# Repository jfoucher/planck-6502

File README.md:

# Planck computer

# An open hardware, extensible 65c02 based computer

This is a hobby computer based on the 65C02 processor. (I use 6502 and 65C02 interchangeably in this document, but [there are some differences](http://wilsonminesco.com/NMOS-CMOSdif/))

There are already many computers based on the 6502 processor, old ones such as as the Apple 1, Apple II, Commodore 64 and many more; and many more recent ones, from homebrew affairs on prototype board, to complete replicas of old systems.

The one that most closely resembles the Planck is probably the RC6502, itself based on the RC2014 (which uses a Z80 processor) with adaptations to the expansion bus to make it fit the 6502 processor.

Planck is a new variant on this type of expandable machines with a different set of tradeoffs.

### Contraints and requirements

The constraints for it's design were the following:

  - Minimum board size, 2 layers, as that is what is cheapest to have fabricated.
  - Easily extensible with for example:
    - Serial port
    - Parallel port
    - SPI / SPI65B port
    - PS/2 port for keyboard
    - Sound card
    - VGA out
    - SD card
    - LCD screen
  - Target clock speed of 10 to 12 MHz

## Some details

These requirements resulted in a computer based on a [motherboard](/Hardware/mainboard) hosting RAM, ROM and CPU and extension slots for expansion cards to plug into.

The [Planck hardware pages](/Hardware) explains more about the functionality of the motherboard and of each basic extension boards.

Of course, you can [design your own expansion boards](/Hardware/make) to make the computer do whatever **you** decide

### Expansion

Each expansion slot has a signal that should cause it to activate (<span style="text-decoration:overline">SEL1</span> to <span style="text-decoration:overline">SEL5</span> as detailed in the expansion bus description). The signals are generated by a programable logic chip on the motherboard (ATF22V10 or equivalent) according to the address that the processor is currently trying to access.

The main computer clock is generated on the motherboard by an oscillator. The clock signal goes through a binary counter, which makes it possible to slow down the clock when accessing slow devices.

The expansion slots are common 2x25 "Dupont" sockets on 2.54mm (100mil) centers and are very easy to obtain.

#### Expansion bus pinout

Most pins correspond to the pins of the same name on the CPU.

Below are the pins that are specific to the expansion bus:

| Pin number | Pin name | Description |
|-----   |-----|--------|
| 1 | A0 | Processor address bus pin 0 |
| 2 | D0 | Processor data bus pin 0 |
| 3 | A1 | Processor address bus pin 1 |
| 4 | D1 | Processor data bus pin 1 |
| 5 | A2 | Processor address bus pin 2 |
| 6 | D2 | Processor data bus pin 2 |
| 7 | A3 | Processor address bus pin 3 |
| 8 | D3 | Processor data bus pin 3 |
| 9 | A4 | Processor address bus pin 4 |
| 10 | D4 | Processor data bus pin 4 |
| 11 | A5 | Processor address bus pin 5 |
| 12 | D5 | Processor data bus pin 5 |
| 13 | A6 | Processor address bus pin 6 |
| 14 | D6 | Processor data bus pin 6 |
| 15 | A7 | Processor address bus pin 7 |
| 16 | D7 | Processor data bus pin 7 |
| 17 | A8 | Processor address bus pin 8 |
| 18 | EX0 | Extra pin for future use or for communication between expansion cards |
| 19 | A9 | Processor address bus pin 9 |
| 20 | EX1 | Extra pin for future use or for communication between expansion cards |
| 21 | A10 | Processor address bus pin 10 |
| 22 | <span style="text-decoration:overline">SLOW</span> | Used by slow peripherals to request a slower clock speed, active low. |
| 23 | GND | Ground |
| 24 | +5V | Positive voltage |
| 25 | +5V | Positive voltage |
| 26 | GND | Ground |
| 27 | A11 | Processor address bus pin 11 |
| 28 | <span style="text-decoration:overline">SSEL</span> | An expansion card is selected. Used by the processor card to disable it's built-in ram an ROM, active low |
| 29 | A12 | Processor address bus pin 12 |
| 30 | <span style="text-decoration:overline">INH</span> | When this is active (low), processor card RAM and ROM are disabled |
| 31 | A13 | Processor address bus pin 13 |
| 32 | <span style="text-decoration:overline">SLOT_SEL</span> | Used by the backplane to signal to expansion cards when they should activate, active low |
| 33 | A14 | Processor address bus pin 14 |
| 34 | LED1 | Connected to one of the backplane LEDs |
| 35 | A15 | Processor address bus pin 15 |
| 36 | LED2 | Connected to one of the backplane LEDs |
| 37 | RDY | Processor I/O pin. When low, the processor waits in it's curent state |
| 38 | LED3 | Connected to one of the backplane LEDs |
| 39 | BE | Processor input pin. when low the processor releases the bus |
| 40 | LED4 | Connected to one of the backplane LEDs |
| 41 | CLK | Main computer clock. Can be stretched or not depending on the state of the SLOW signal. |
| 42 | CLK_12M | Stable clock for e.g. VIA timers. **Not connected to slot 0** |
| 43 | R<span style="text-decoration:overline">W</span> | CPU read / write pin |
| 44 | EX4 | Extra signal 4. **Not connected to slot 0** |
| 45 | <span style="text-decoration:overline">IRQ</span> | This goes low when an interrupt request has occured, active low |
| 46 | EX5 | Extra signal 5. **Not connected to slot 0** |
| 47 | SYNC | CPU output. Indicates when the CPU is fetching an opcode |
| 48 | <span style="text-decoration:overline">SLOT_IRQ</span> | Used by expansion cards to signal an interrupt request to the processor board, active low  |
| 49 | <span style="text-decoration:overline">RESET</span> | Reset signal trigered by the button on the backplane, active low |
| 50 | <span style="text-decoration:overline">NMI</span> | non maskable interrupt signal trigered by the button on the backplane, active low |

The Planck 6502 computer is a single board computer that communicates over serial, or can be a standalone computer by adding expansion cards to one of the 6 slots present on the motherboard.

### Input / output
Also present on the motherboard are two buttons and 4 LEDs.

One button triggers a reset of the processor, and the other triggers an non-maskable interrupt (<span style="text-decoration:overline">NMI</span>) which can be thought of as a "soft" reset.

The leds are connected to the expansion bus, and so any board can control them. They can be used as a crude debug tool, to show the status of some processing, to try out a simple blink routine or to signal an error to the user.

### Power delivery

The power to the board is provided by a barrel jack at the bottom left. There is a linear regulator on the board, so the power supply voltage can be anywhere from 7V to 12V, although with the latter a heatsink may be required on the regulator.

A power switch and a power LED are also provided on the backplane.

## Available expansion boards

### I/O board

[The IO board](Hardware/io_board) is based on a WDC65C22 chip and provides a keyboard PS/2 port, a parallel port and a 65SIB port (serial port similar to and compatible with SPI)

### Serial board

[The serial board](Hardware/serial_board) is based on a WDC65C51 chip and provides serial output through a TTL serial to USB adapter. When plugging the USB cable to your PC, it may be best to unplug the power from the backplane and let the computer be powered from your PC through the USB to serial adapter.

### OPL2 board

[A sound card](Hardware/opl2_board) based on the Yamaha OPL2 chip found in the original sound blaster card for example.

### LCD board

[This board](Hardware/lcd_board) allow a 20x04 LCD to be connected to the computer for text output.

<br />This documentation is licensed under a <a rel="license" href="http://creativecommons.org/licenses/by-sa/4.0/">Creative Commons Attribution-ShareAlike 4.0 International License</a>.

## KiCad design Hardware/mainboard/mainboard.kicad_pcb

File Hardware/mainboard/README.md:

## Planck computer

This is a complete computer based on the Planck 6502 backplane.

It provides a 65c02 cPU, 32k of RAM, 32k of ROM and a serial port, as well as 6 expansion slots.

The board exceeds the original size specification of the original project (100 x 150mm instead of 100 x 100mm) but it seems that the cost will be similar (one more expensive board replaces 3 cheaper boards) as well as being more practical for some applications.

This computer can run absolutely stand alone when connected via the serial port. It can also accommodate 2 more expansion cards compared to the original backplane.

Here is a 3D view of the board:

You can [download the schematic](https://planck6502.com/fabrication/mainboard-schematic.pdf) and the [gerber files](https://planck6502.com/fabrication/mainboard-zip.zip)

[Documentation](https://planck6502.com/Hardware/io/)

<br />This documentation is licensed under a <a rel="license" href="http://creativecommons.org/licenses/by-sa/4.0/">Creative Commons Attribution-ShareAlike 4.0 International License</a>.

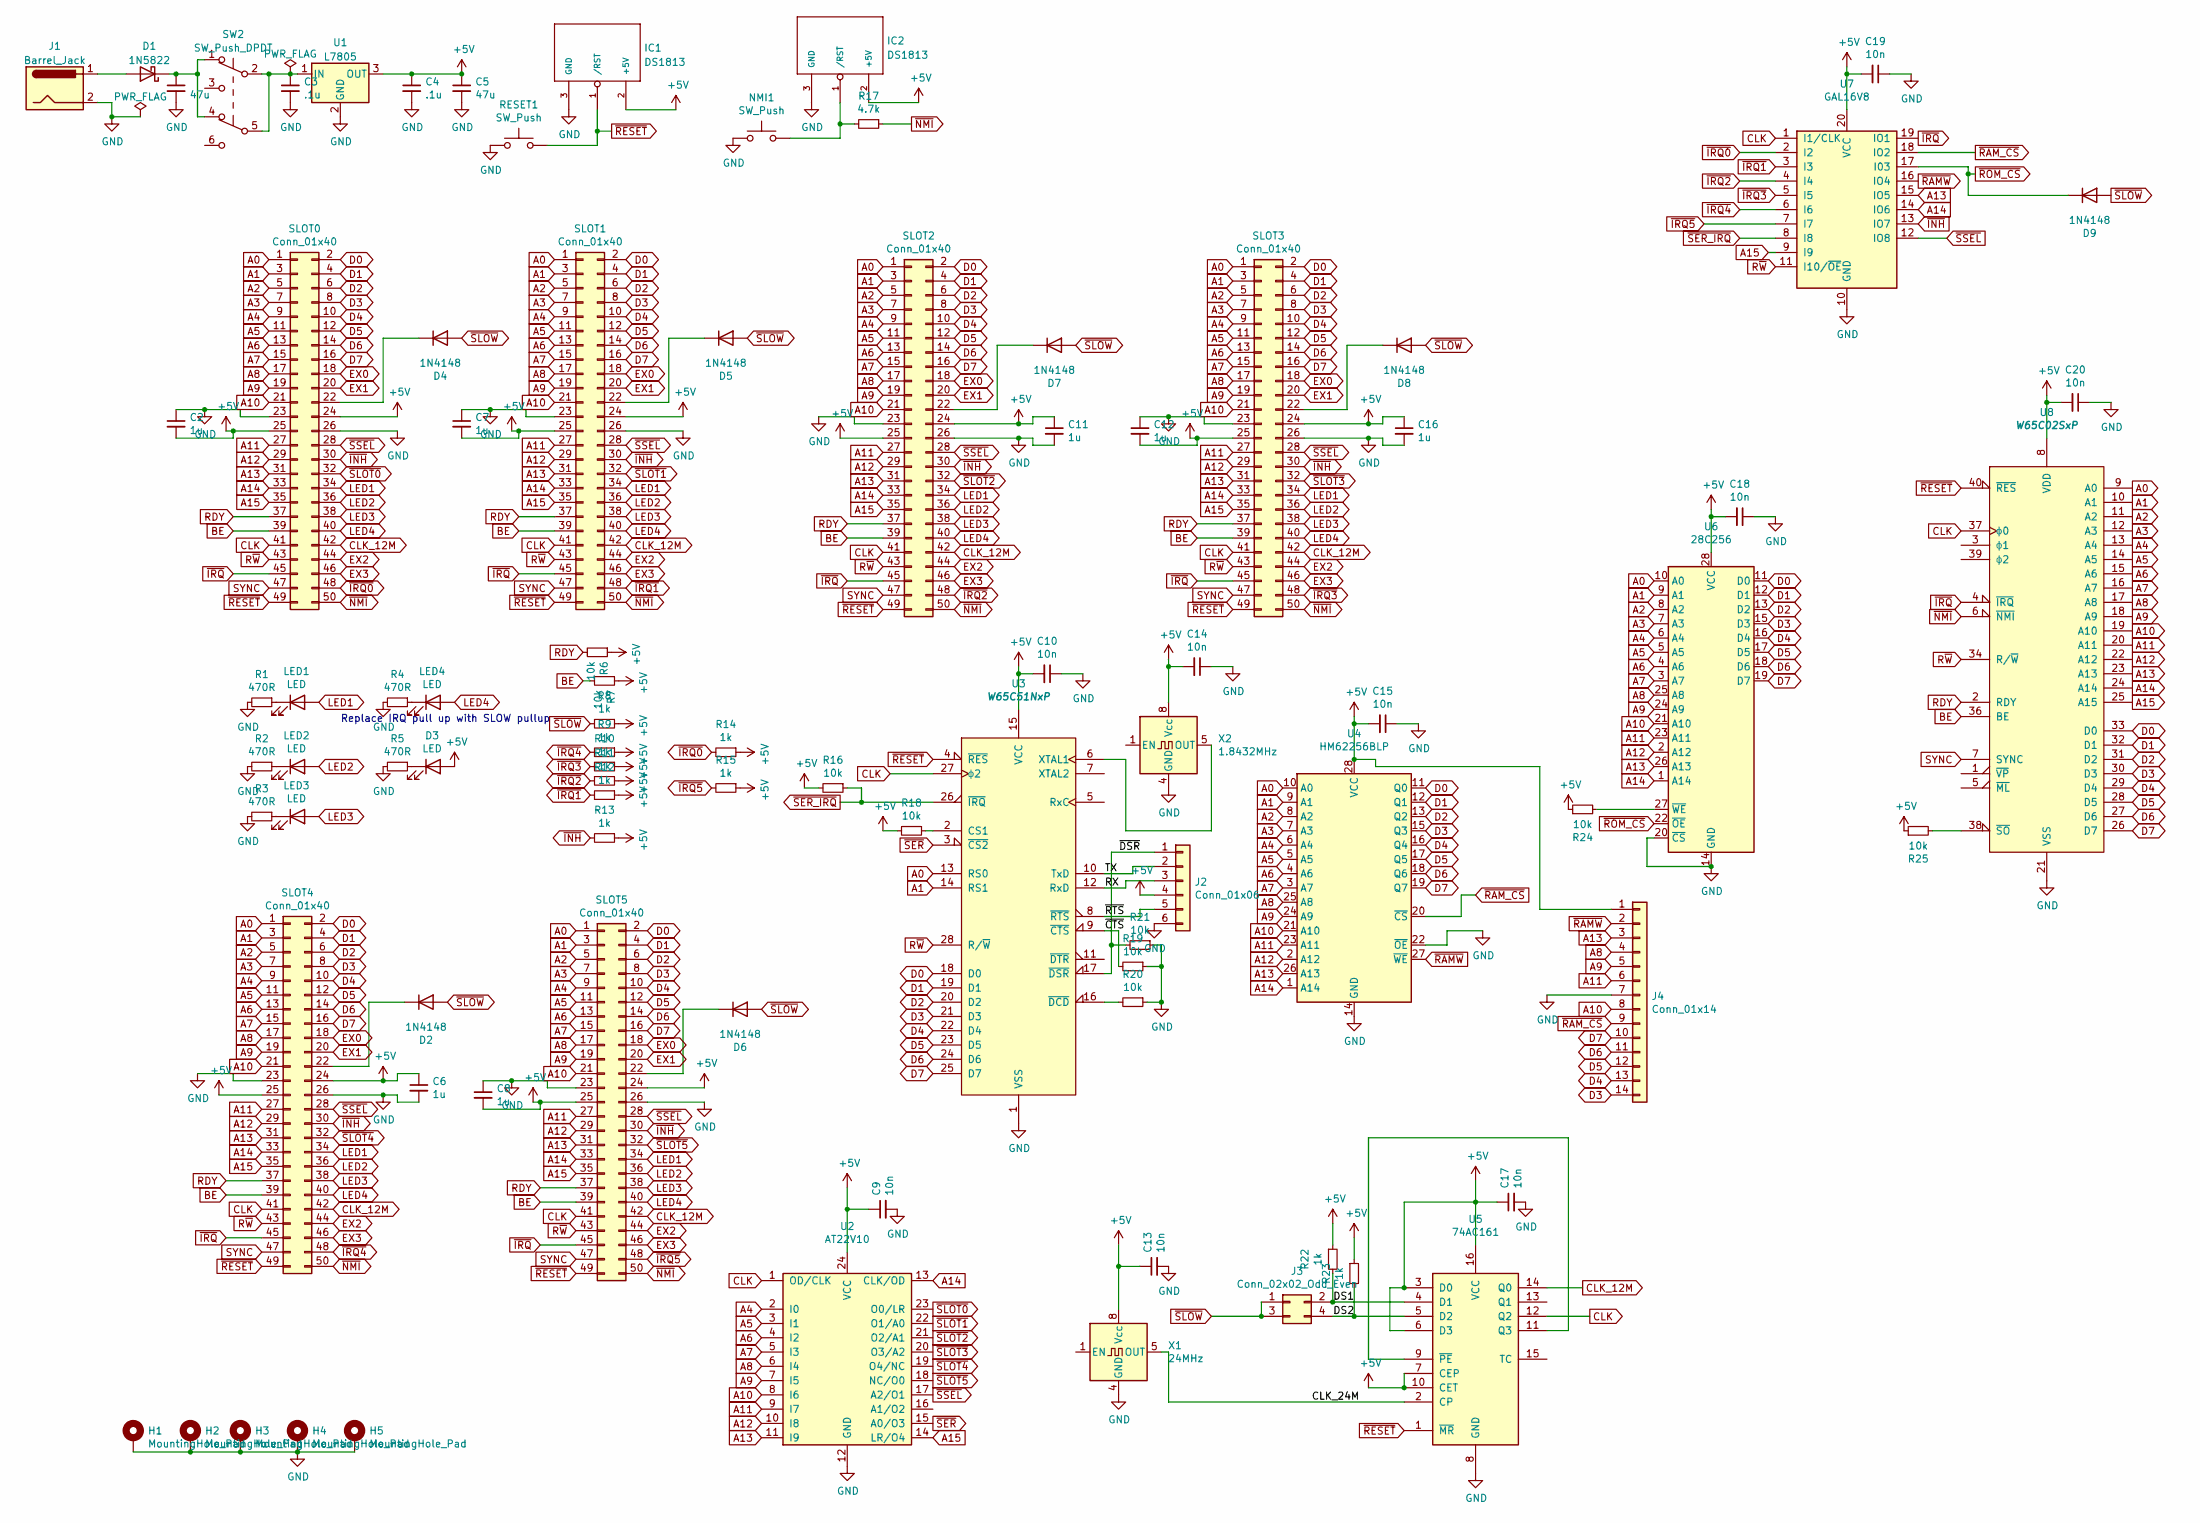
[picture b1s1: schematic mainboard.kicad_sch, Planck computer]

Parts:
C1, C5: 47u; CP_Radial_D4.0mm_P2.00mm
C2, C6, C7, C8, C11, C12, C16: 1u; C_Disc_D4.3mm_W1.9mm_P5.00mm
C3, C4: .1u; C_Disc_D4.3mm_W1.9mm_P5.00mm
C9, C10, C13, C14, C15, C17, C18, C19, C20: 10n; C_Disc_D4.3mm_W1.9mm_P5.00mm
D1: 1N5822; D_DO-201AD_P15.24mm_Horizontal
D2, D4, D5, D6, D7, D8, D9: 1N4148; D_DO-35_SOD27_P7.62mm_Horizontal
D3: LED; LED_D3.0mm
H1, H2, H3, H4, H5: MountingHole_Pad; MountingHole_3.2mm_M3_Pad
IC1, IC2: DS1813; TO-92_Inline_Wide
J1: Barrel_Jack; BarrelJack_Horizontal
J2: Conn_01x06; PinSocket_1x06_P2.54mm_Vertical
J3: Conn_02x02_Odd_Even; PinHeader_2x02_P2.54mm_Vertical
J4: Conn_01x14; PinSocket_1x14_P2.54mm_Vertical
LED1, LED2, LED3, LED4: LED; LED_D3.0mm
NMI1: SW_Push; SW_PUSH_6mm
R1, R2, R3, R4, R5: 470R; R_Axial_DIN0207_L6.3mm_D2.5mm_P7.62mm_Horizontal
R6, R7, R16, R18, R19, R20, R21, R24, R25: 10k; R_Axial_DIN0207_L6.3mm_D2.5mm_P7.62mm_Horizontal
R8, R9, R10, R11, R12, R13, R14, R15, R22, R23: 1k; R_Axial_DIN0207_L6.3mm_D2.5mm_P7.62mm_Horizontal
R17: 4.7k; R_Axial_DIN0207_L6.3mm_D2.5mm_P7.62mm_Horizontal
RESET1: SW_Push; SW_PUSH_6mm
SLOT0, SLOT1, SLOT2, SLOT3, SLOT4, SLOT5: Conn_01x40; PinSocket_2x25_P2.54mm_Vertical
SW2: SW_Push_DPDT; SW_E-Switch_EG1271_SPDT
U1: L7805; TO-220-3_Vertical
U2: AT22V10; DIP-24_W7.62mm_Socket
U3: W65C51NxP; DIP-28_W15.24mm_Socket
U4: HM62256BLP; DIP-28_W7.62mm_Socket
U5: 74AC161; DIP-16_W7.62mm_Socket
U6: 28C256; DIP-28_W15.24mm_Socket
U7: GAL16V8; DIP-20_W7.62mm_Socket
U8: W65C02SxP; DIP-40_W15.24mm_Socket
X1: 24MHz; Oscillator_DIP-8
X2: 1.8432MHz; Oscillator_DIP-8

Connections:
+5V: C2.2, C4.1, C5.1, C6.1, C7.2, C8.2, C9.1, C10.2, C11.1, C12.2, C13.1, C14.2, C15.2, C16.1, C17.1, C18.2, C19.2, C20.2, D3.2 (A), IC1.2 (+5V), IC2.2 (+5V), J2.4, J4.1, R6.1, R7.1, R8.1, R9.1, R10.1, R11.1, R12.1, R13.1, R14.1, R15.1, R16.2, R18.2, R22.1, R23.1, R24.1, R25.1, SLOT0.24, SLOT0.25, SLOT1.24, SLOT1.25, SLOT2.24, SLOT2.25, SLOT3.24, SLOT3.25, SLOT4.24, SLOT4.25, SLOT5.24, SLOT5.25, U1.3 (OUT), U2.24 (VCC), U3.15 (VCC), U4.28 (VCC), U5.3 (D0), U5.6 (D3), U5.7 (CEP), U5.10 (CET), U5.16 (VCC), U6.28 (VCC), U7.20 (VCC), U8.8 (VDD), X1.8 (Vcc), X2.8 (Vcc)
/CLK_24M: U5.2 (CP), X1.5 (OUT)
/DS1: J3.2, R22.2, U5.4 (D1)
/DS2: J3.4, R23.2, U5.5 (D2)
/RX: J2.3, U3.12 (RxD)
/TX: J2.2, U3.10 (TxD)
/~CTS: R19.2, U3.9 (~CTS)
/~DSR: J2.1, R21.2, U3.17 (~DSR)
/~RTS: J2.5, U3.8 (~RTS)
A0: SLOT0.1, SLOT1.1, SLOT2.1, SLOT3.1, SLOT4.1, SLOT5.1, U3.13 (RS0), U4.10 (A0), U6.10 (A0), U8.9 (A0)
A1: SLOT0.3, SLOT1.3, SLOT2.3, SLOT3.3, SLOT4.3, SLOT5.3, U3.14 (RS1), U4.9 (A1), U6.9 (A1), U8.10 (A1)
A2: SLOT0.5, SLOT1.5, SLOT2.5, SLOT3.5, SLOT4.5, SLOT5.5, U4.8 (A2), U6.8 (A2), U8.11 (A2)
A3: SLOT0.7, SLOT1.7, SLOT2.7, SLOT3.7, SLOT4.7, SLOT5.7, U4.7 (A3), U6.7 (A3), U8.12 (A3)
A4: SLOT0.9, SLOT1.9, SLOT2.9, SLOT3.9, SLOT4.9, SLOT5.9, U2.2 (I0), U4.6 (A4), U6.6 (A4), U8.13 (A4)
A5: SLOT0.11, SLOT1.11, SLOT2.11, SLOT3.11, SLOT4.11, SLOT5.11, U2.3 (I1), U4.5 (A5), U6.5 (A5), U8.14 (A5)
A6: SLOT0.13, SLOT1.13, SLOT2.13, SLOT3.13, SLOT4.13, SLOT5.13, U2.4 (I2), U4.4 (A6), U6.4 (A6), U8.15 (A6)
A7: SLOT0.15, SLOT1.15, SLOT2.15, SLOT3.15, SLOT4.15, SLOT5.15, U2.5 (I3), U4.3 (A7), U6.3 (A7), U8.16 (A7)
A8: J4.4, SLOT0.17, SLOT1.17, SLOT2.17, SLOT3.17, SLOT4.17, SLOT5.17, U2.6 (I4), U4.25 (A8), U6.25 (A8), U8.17 (A8)
A9: J4.5, SLOT0.19, SLOT1.19, SLOT2.19, SLOT3.19, SLOT4.19, SLOT5.19, U2.7 (I5), U4.24 (A9), U6.24 (A9), U8.18 (A9)
A10: J4.8, SLOT0.21, SLOT1.21, SLOT2.21, SLOT3.21, SLOT4.21, SLOT5.21, U2.8 (I6), U4.21 (A10), U6.21 (A10), U8.19 (A10)
A11: J4.6, SLOT0.27, SLOT1.27, SLOT2.27, SLOT3.27, SLOT4.27, SLOT5.27, U2.9 (I7), U4.23 (A11), U6.23 (A11), U8.20 (A11)
A12: SLOT0.29, SLOT1.29, SLOT2.29, SLOT3.29, SLOT4.29, SLOT5.29, U2.10 (I8), U4.2 (A12), U6.2 (A12), U8.22 (A12)
A13: J4.3, SLOT0.31, SLOT1.31, SLOT2.31, SLOT3.31, SLOT4.31, SLOT5.31, U2.11 (I9), U4.26 (A13), U6.26 (A13), U7.15 (IO5), U8.23 (A13)
A14: SLOT0.33, SLOT1.33, SLOT2.33, SLOT3.33, SLOT4.33, SLOT5.33, U2.13 (CLK/OD), U4.1 (A14), U6.1 (A14), U7.14 (IO6), U8.24 (A14)
A15: SLOT0.35, SLOT1.35, SLOT2.35, SLOT3.35, SLOT4.35, SLOT5.35, U2.14 (LR/O4), U7.9 (I9), U8.25 (A15)
BE: R7.2, SLOT0.39, SLOT1.39, SLOT2.39, SLOT3.39, SLOT4.39, SLOT5.39, U8.36 (BE)
CLK: SLOT0.41, SLOT1.41, SLOT2.41, SLOT3.41, SLOT4.41, SLOT5.41, U2.1 (OD/CLK), U3.27 (ϕ2), U5.12 (Q2), U7.1 (I1/CLK), U8.37 (ϕ0)
CLK_12M: SLOT0.42, SLOT1.42, SLOT2.42, SLOT3.42, SLOT4.42, SLOT5.42, U5.14 (Q0)
D0: SLOT0.2, SLOT1.2, SLOT2.2, SLOT3.2, SLOT4.2, SLOT5.2, U3.18 (D0), U4.11 (Q0), U6.11 (D0), U8.33 (D0)
D1: SLOT0.4, SLOT1.4, SLOT2.4, SLOT3.4, SLOT4.4, SLOT5.4, U3.19 (D1), U4.12 (Q1), U6.12 (D1), U8.32 (D1)
D2: SLOT0.6, SLOT1.6, SLOT2.6, SLOT3.6, SLOT4.6, SLOT5.6, U3.20 (D2), U4.13 (Q2), U6.13 (D2), U8.31 (D2)
D3: J4.14, SLOT0.8, SLOT1.8, SLOT2.8, SLOT3.8, SLOT4.8, SLOT5.8, U3.21 (D3), U4.15 (Q3), U6.15 (D3), U8.30 (D3)
D4: J4.13, SLOT0.10, SLOT1.10, SLOT2.10, SLOT3.10, SLOT4.10, SLOT5.10, U3.22 (D4), U4.16 (Q4), U6.16 (D4), U8.29 (D4)
D5: J4.12, SLOT0.12, SLOT1.12, SLOT2.12, SLOT3.12, SLOT4.12, SLOT5.12, U3.23 (D5), U4.17 (Q5), U6.17 (D5), U8.28 (D5)
D6: J4.11, SLOT0.14, SLOT1.14, SLOT2.14, SLOT3.14, SLOT4.14, SLOT5.14, U3.24 (D6), U4.18 (Q6), U6.18 (D6), U8.27 (D6)
D7: J4.10, SLOT0.16, SLOT1.16, SLOT2.16, SLOT3.16, SLOT4.16, SLOT5.16, U3.25 (D7), U4.19 (Q7), U6.19 (D7), U8.26 (D7)
EX0: SLOT0.18, SLOT1.18, SLOT2.18, SLOT3.18, SLOT4.18, SLOT5.18
EX1: SLOT0.20, SLOT1.20, SLOT2.20, SLOT3.20, SLOT4.20, SLOT5.20
EX2: SLOT0.44, SLOT1.44, SLOT2.44, SLOT3.44, SLOT4.44, SLOT5.44
EX3: SLOT0.46, SLOT1.46, SLOT2.46, SLOT3.46, SLOT4.46, SLOT5.46
GND: C1.2, C2.1, C3.2, C4.2, C5.2, C6.2, C7.1, C8.1, C9.2, C10.1, C11.2, C12.1, C13.2, C14.1, C15.1, C16.2, C17.2, C18.1, C19.1, C20.1, H1.1, H2.1, H3.1, H4.1, H5.1, IC1.3 (GND), IC2.3 (GND), J1.2, J2.6, J4.7, NMI1.1, R1.2, R2.2, R3.2, R4.2, R5.2, R19.1, R20.1, R21.1, RESET1.1, SLOT0.23, SLOT0.26, SLOT1.23, SLOT1.26, SLOT2.23, SLOT2.26, SLOT3.23, SLOT3.26, SLOT4.23, SLOT4.26, SLOT5.23, SLOT5.26, U1.2 (GND), U2.12 (GND), U3.1 (VSS), U4.14 (GND), U4.22 (~OE), U5.8 (GND), U6.14 (GND), U6.20 (~CS), U7.10 (GND), U8.21 (VSS), X1.4 (GND), X2.4 (GND)
LED1: LED1.2 (A), SLOT0.34, SLOT1.34, SLOT2.34, SLOT3.34, SLOT4.34, SLOT5.34
LED2: LED2.2 (A), SLOT0.36, SLOT1.36, SLOT2.36, SLOT3.36, SLOT4.36, SLOT5.36
LED3: LED3.2 (A), SLOT0.38, SLOT1.38, SLOT2.38, SLOT3.38, SLOT4.38, SLOT5.38
LED4: LED4.2 (A), SLOT0.40, SLOT1.40, SLOT2.40, SLOT3.40, SLOT4.40, SLOT5.40
unnamed: D1.2 (A), J1.1
unnamed: C1.1, D1.1 (K), SW2.1 (A), SW2.4 (A)
unnamed: D2.1 (K), SLOT4.22
unnamed: D3.1 (K), R5.1
unnamed: D4.1 (K), SLOT0.22
unnamed: D5.1 (K), SLOT1.22
unnamed: D6.1 (K), SLOT5.22
unnamed: D7.1 (K), SLOT2.22
unnamed: D8.1 (K), SLOT3.22
unnamed: IC2.1 (/RST), NMI1.2, R17.2
unnamed: LED1.1 (K), R1.1
unnamed: LED2.1 (K), R2.1
unnamed: LED3.1 (K), R3.1
unnamed: LED4.1 (K), R4.1
unnamed: C3.1, SW2.2 (B), SW2.5 (B), U1.1 (IN)
unnamed: R18.1, U3.2 (CS1)
unnamed: U3.6 (XTAL1), X2.5 (OUT)
unnamed: R20.2, U3.16 (~DCD)
unnamed: U5.9 (~PE), U5.11 (Q3)
unnamed: R24.2, U6.27 (~WE)
unnamed: R25.2, U8.38 (~SO)
RDY: R6.2, SLOT0.37, SLOT1.37, SLOT2.37, SLOT3.37, SLOT4.37, SLOT5.37, U8.2 (RDY)
R~W: SLOT0.43, SLOT1.43, SLOT2.43, SLOT3.43, SLOT4.43, SLOT5.43, U3.28 (R/~W), U7.11 (I10/~OE), U8.34 (R/~W)
SYNC: SLOT0.47, SLOT1.47, SLOT2.47, SLOT3.47, SLOT4.47, SLOT5.47, U8.7 (SYNC)
~INH: R13.2, SLOT0.30, SLOT1.30, SLOT2.30, SLOT3.30, SLOT4.30, SLOT5.30, U7.13 (IO7)
~IRQ0: R14.2, SLOT0.48, U7.2 (I2)
~IRQ1: R12.2, SLOT1.48, U7.3 (I3)
~IRQ2: R11.2, SLOT2.48, U7.4 (I4)
~IRQ3: R10.2, SLOT3.48, U7.5 (I5)
~IRQ4: R9.2, SLOT4.48, U7.6 (I6)
~IRQ5: R15.2, SLOT5.48, U7.7 (I7)
~IRQ: SLOT0.45, SLOT1.45, SLOT2.45, SLOT3.45, SLOT4.45, SLOT5.45, U7.19 (IO1), U8.4 (~IRQ)
~NMI: R17.1, SLOT0.50, SLOT1.50, SLOT2.50, SLOT3.50, SLOT4.50, SLOT5.50, U8.6 (~NMI)
~RAMW: J4.2, U4.27 (~WE), U7.16 (IO4)
~RAM_CS: J4.9, U4.20 (~CS), U7.18 (IO2)
~RESET: IC1.1 (/RST), RESET1.2, SLOT0.49, SLOT1.49, SLOT2.49, SLOT3.49, SLOT4.49, SLOT5.49, U3.4 (~RES), U5.1 (~MR), U8.40 (~RES)
~ROM_CS: D9.1 (K), U6.22 (~OE), U7.17 (I03)
~SER_IRQ: R16.1, U3.26 (~IRQ), U7.8 (I8)
~SER: U2.15 (A0/O3), U3.3 (~CS2)
~SLOT0: SLOT0.32, U2.23 (O0/LR)
~SLOT1: SLOT1.32, U2.22 (O1/A0)
~SLOT2: SLOT2.32, U2.21 (O2/A1)
~SLOT3: SLOT3.32, U2.20 (O3/A2)
~SLOT4: SLOT4.32, U2.19 (O4/NC)
~SLOT5: SLOT5.32, U2.18 (NC/O0)
~SLOW: D2.2 (A), D4.2 (A), D5.2 (A), D6.2 (A), D7.2 (A), D8.2 (A), D9.2 (A), J3.1, J3.3, R8.2
~SSEL: SLOT0.28, SLOT1.28, SLOT2.28, SLOT3.28, SLOT4.28, SLOT5.28, U2.17 (A2/O1), U7.12 (IO8)

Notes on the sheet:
Replace IRQ pull up with SLOW pullup

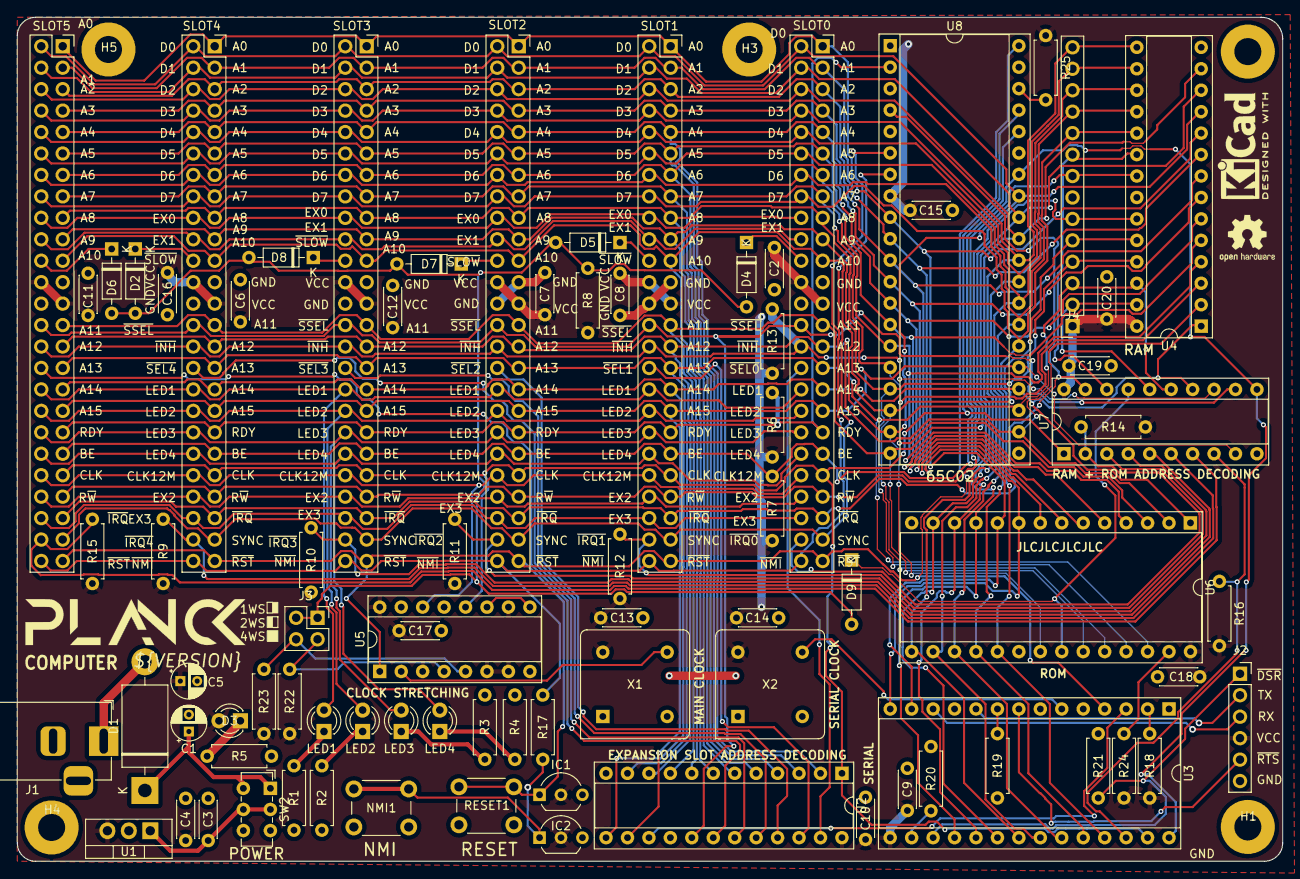
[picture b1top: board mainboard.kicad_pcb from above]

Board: 2 copper layers, 149.9 x 99.9 mm, 88 parts (0 on the bottom side), 92 nets.

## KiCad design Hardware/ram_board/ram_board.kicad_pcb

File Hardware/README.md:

## Hardware

In this folder you will find all the schematics and board layouts in [Kicad](https://www.kicad.org/) format.

You probably want to take a look at the [main board](mainboard/) first as that explains the basic architecture of the computer.

<br />This documentation is licensed under a <a rel="license" href="http://creativecommons.org/licenses/by-sa/4.0/">Creative Commons Attribution-ShareAlike 4.0 International License</a>.

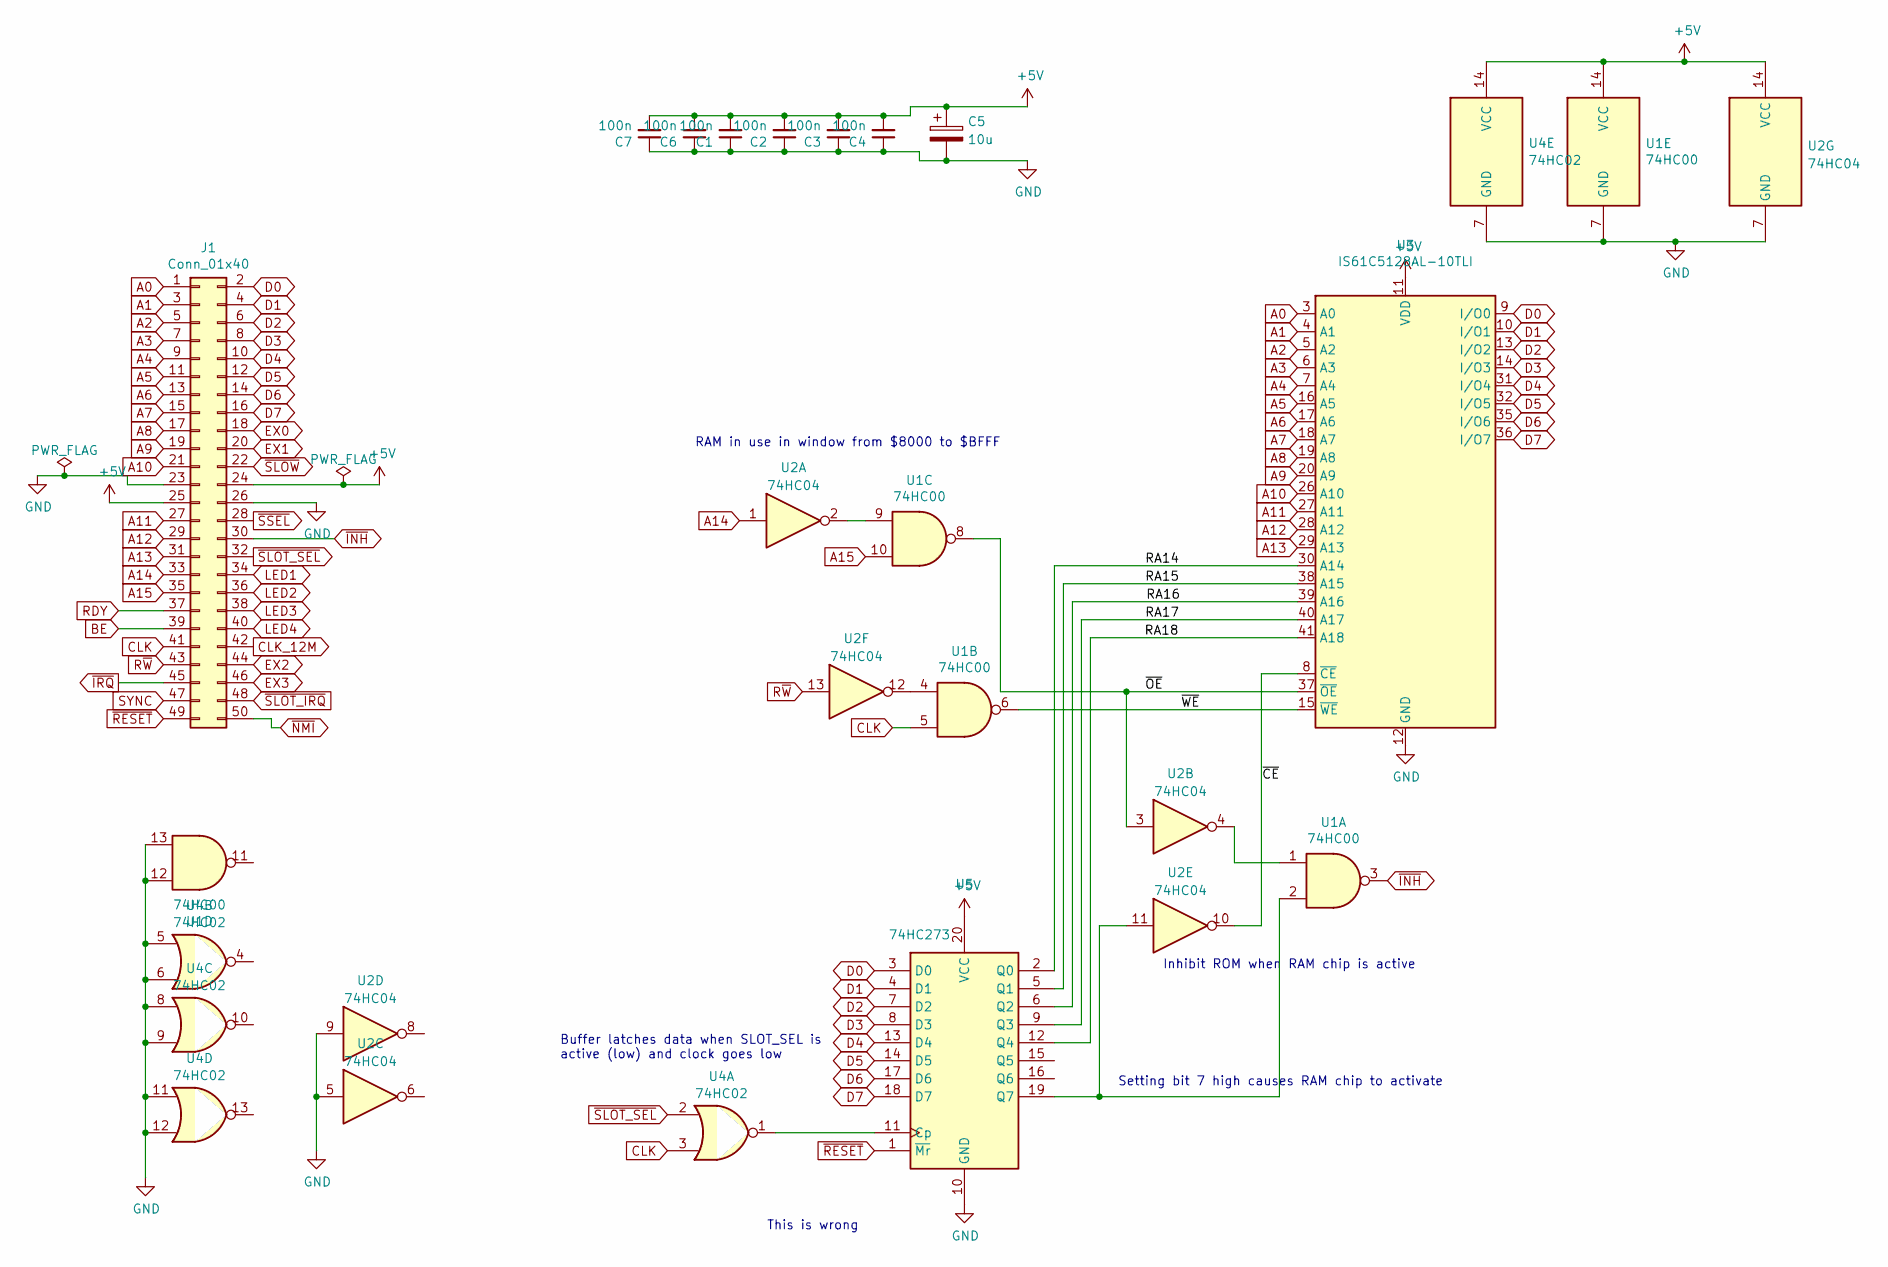
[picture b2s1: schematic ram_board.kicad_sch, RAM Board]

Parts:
C1, C2, C3, C4, C6, C7: 100n; C_Disc_D4.3mm_W1.9mm_P5.00mm
C5: 10u; C_Radial_D5.0mm_H11.0mm_P2.00mm
J1: Conn_01x40; PinHeader_2x25_P2.54mm_Horizontal
U1: 74HC00; DIP-14_W7.62mm_Socket
U2: 74HC04; DIP-14_W7.62mm_Socket
U3: IS61C5128AL-10TLI; TSOP-II-44_10.16x18.41mm_P0.8mm
U4: 74HC02; DIP-14_W7.62mm_Socket
U5: 74HC273; DIP-20_W7.62mm_Socket

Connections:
+5V: C1.2, C2.2, C3.2, C4.2, C5.1, C6.2, C7.2, J1.24, J1.25, U1.14 (VCC), U2.14 (VCC), U3.11 (VDD), U3.33 (VDD), U4.14 (VCC), U5.20 (VCC)
/RA14: U3.30 (A14), U5.2 (Q0)
/RA15: U3.38 (A15), U5.5 (Q1)
/RA16: U3.39 (A16), U5.6 (Q2)
/RA17: U3.40 (A17), U5.9 (Q3)
/RA18: U3.41 (A18), U5.12 (Q4)
/~CE: U2.10, U3.8 (~CE)
/~OE: U1.8, U2.3, U3.37 (~OE)
/~WE: U1.6, U3.15 (~WE)
A0: J1.1, U3.3 (A0)
A1: J1.3, U3.4 (A1)
A2: J1.5, U3.5 (A2)
A3: J1.7, U3.6 (A3)
A4: J1.9, U3.7 (A4)
A5: J1.11, U3.16 (A5)
A6: J1.13, U3.17 (A6)
A7: J1.15, U3.18 (A7)
A8: J1.17, U3.19 (A8)
A9: J1.19, U3.20 (A9)
A10: J1.21, U3.26 (A10)
A11: J1.27, U3.27 (A11)
A12: J1.29, U3.28 (A12)
A13: J1.31, U3.29 (A13)
A14: J1.33, U2.1
A15: J1.35, U1.10
BE: J1.39
CLK: J1.41, U1.5, U4.3
CLK_12M: J1.42
D0: J1.2, U3.9 (I/O0), U5.3 (D0)
D1: J1.4, U3.10 (I/O1), U5.4 (D1)
D2: J1.6, U3.13 (I/O2), U5.7 (D2)
D3: J1.8, U3.14 (I/O3), U5.8 (D3)
D4: J1.10, U3.31 (I/O4), U5.13 (D4)
D5: J1.12, U3.32 (I/O5), U5.14 (D5)
D6: J1.14, U3.35 (I/O6), U5.17 (D6)
D7: J1.16, U3.36 (I/O7), U5.18 (D7)
EX0: J1.18
EX1: J1.20
EX2: J1.44
EX3: J1.46
GND: C1.1, C2.1, C3.1, C4.1, C5.2, C6.1, C7.1, J1.23, J1.26, U1.7 (GND), U1.12, U1.13, U2.5, U2.7 (GND), U2.9, U3.12 (GND), U3.34 (GND), U4.5, U4.6, U4.7 (GND), U4.8, U4.9, U4.11, U4.12, U5.10 (GND)
LED1: J1.34
LED2: J1.36
LED3: J1.38
LED4: J1.40
unnamed: U1.1, U2.4
unnamed: U1.4, U2.12
unnamed: U1.9, U2.2
unnamed: U4.1, U5.11 (Cp)
unnamed: U1.2, U2.11, U5.19 (Q7)
RDY: J1.37
R~W: J1.43, U2.13
SYNC: J1.47
~INH: J1.30, U1.3
~IRQ: J1.45
~NMI: J1.50
~RESET: J1.49, U5.1 (~Mr)
~SLOT_IRQ: J1.48
~SLOT_SEL: J1.32, U4.2
~SLOW: J1.22
~SSEL: J1.28

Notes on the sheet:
Inhibit ROM when RAM chip is active
This is wrong
RAM in use in window from $8000 to $BFFF
Buffer latches data when SLOT_SEL is active (low) and clock goes low
Setting bit 7 high causes RAM chip to activate

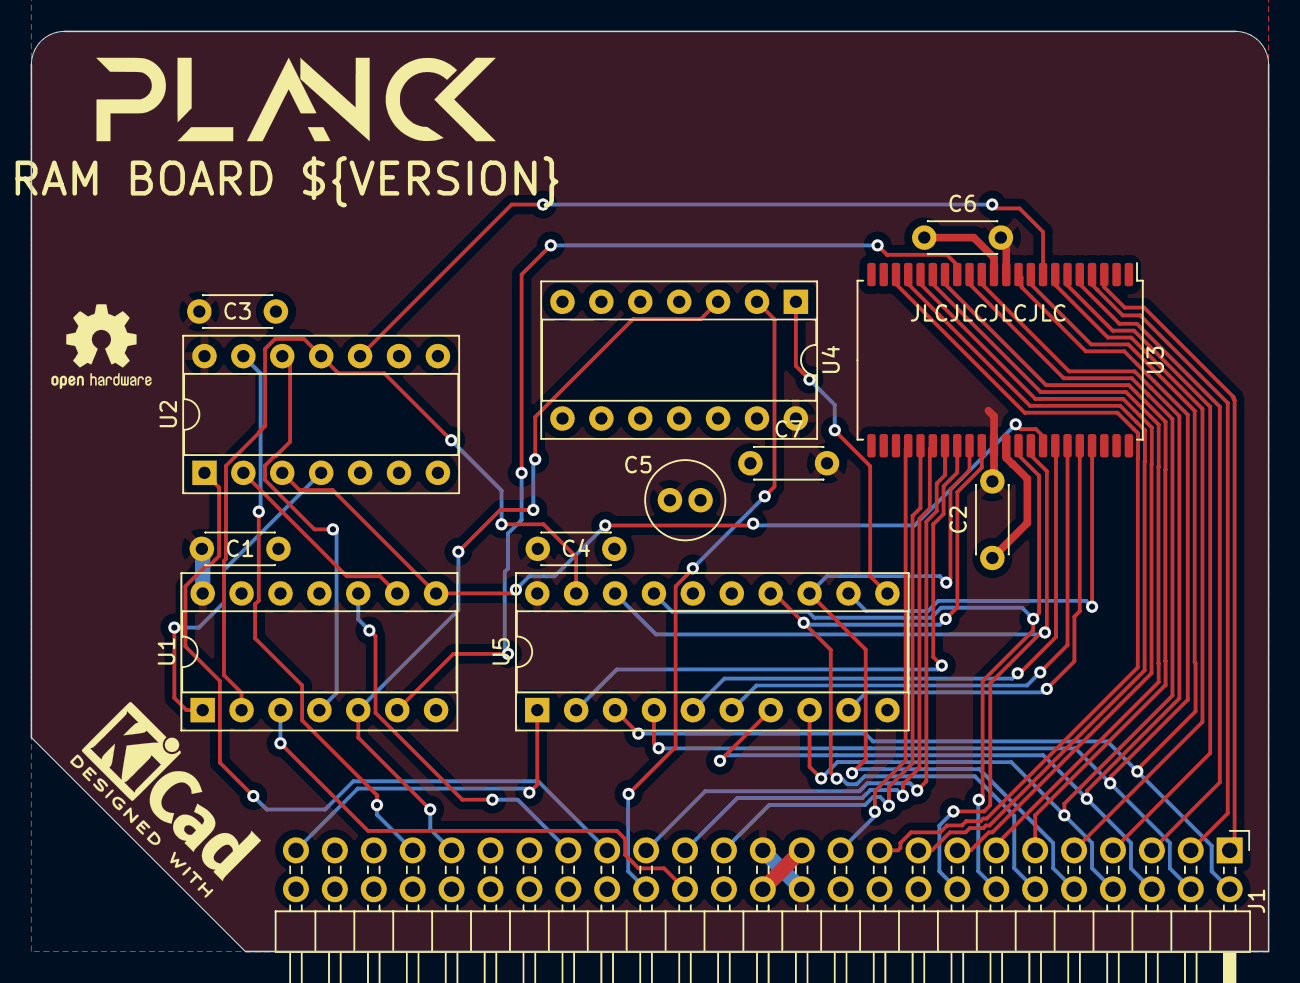
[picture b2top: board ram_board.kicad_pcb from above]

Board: 2 copper layers, 80.8 x 60.1 mm, 16 parts (1 on the bottom side), 44 nets.

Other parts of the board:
LOGO, LOGO2: LOGO; logo
OSHW: OSHW-Logo2_7.3x6mm_SilkScreen

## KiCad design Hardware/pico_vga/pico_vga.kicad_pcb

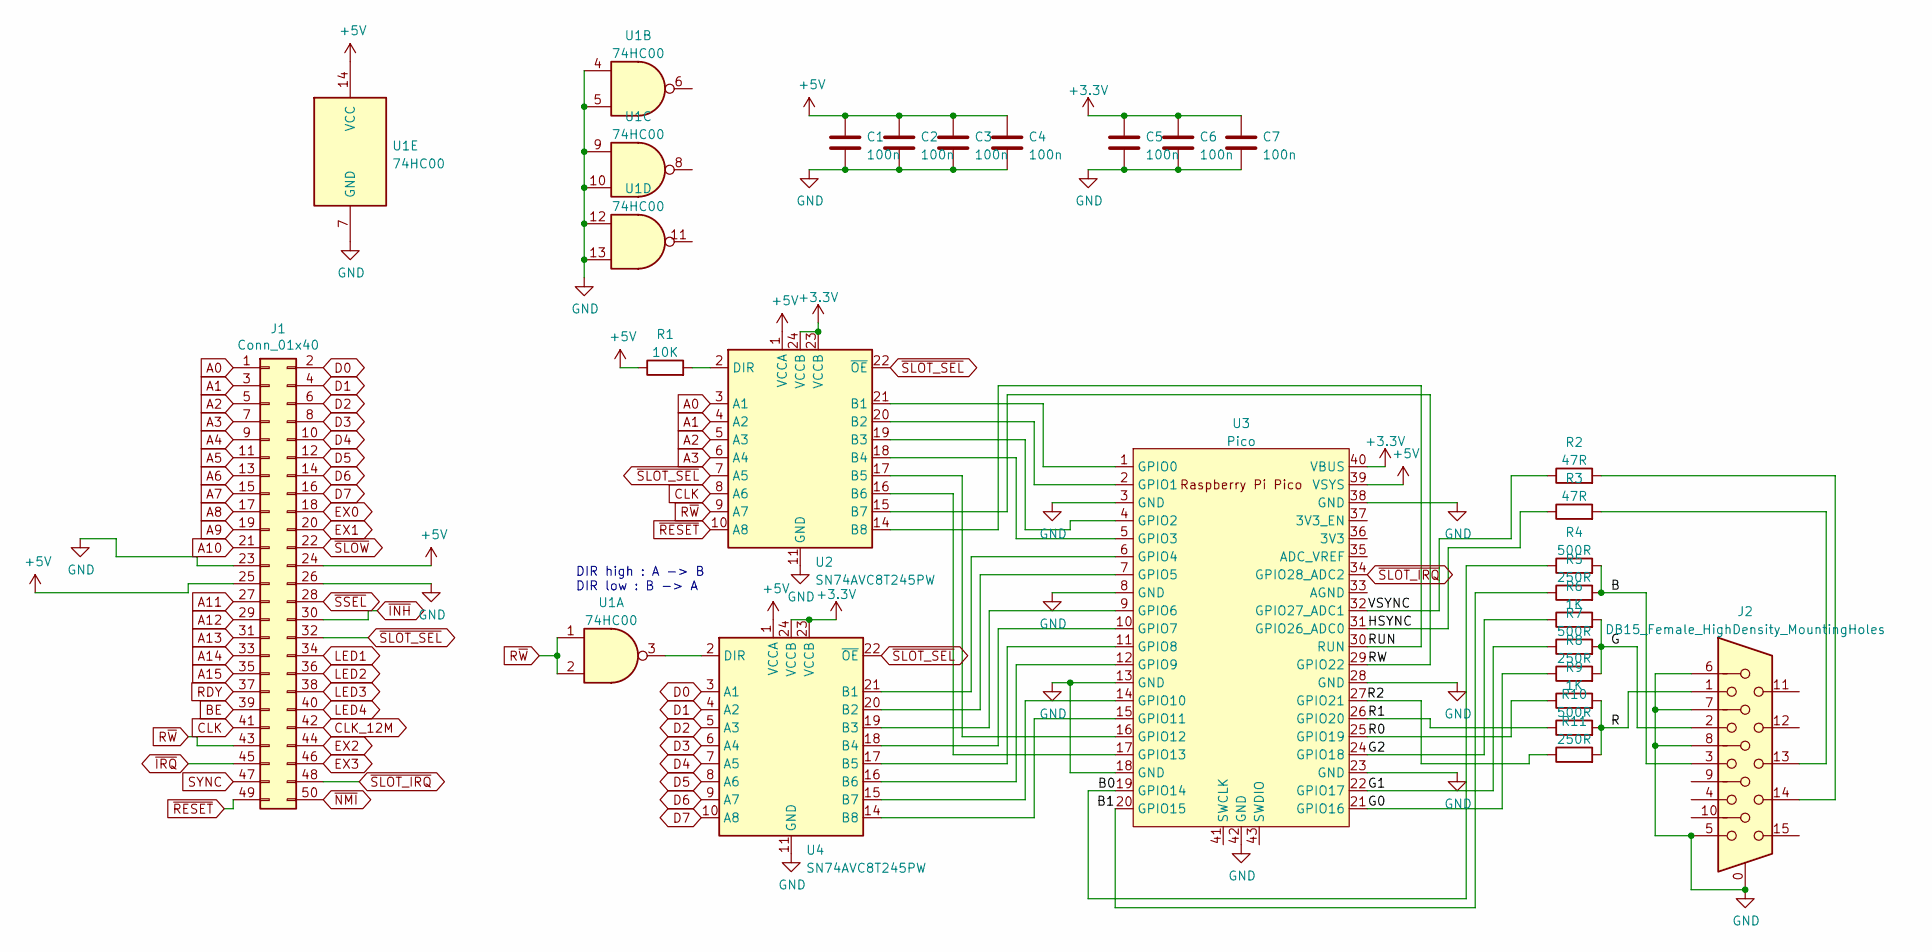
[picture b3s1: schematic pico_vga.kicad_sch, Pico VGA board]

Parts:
C1, C2, C3, C4, C5, C6, C7: 100n; C_Disc_D5.0mm_W2.5mm_P5.00mm
J1: Conn_01x40; PinHeader_2x25_P2.54mm_Horizontal
J2: DB15_Female_HighDensity_MountingHoles; DSUB-15-HD_Female_Horizontal_P2.29x1.98mm_EdgePinOffset3.03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
R1: 10K; R_Axial_DIN0309_L9.0mm_D3.2mm_P12.70mm_Horizontal
R2, R3: 47R; R_Axial_DIN0309_L9.0mm_D3.2mm_P2.54mm_Vertical
R4, R7, R10: 500R; R_Axial_DIN0309_L9.0mm_D3.2mm_P2.54mm_Vertical
R5, R8, R11: 250R; R_Axial_DIN0309_L9.0mm_D3.2mm_P2.54mm_Vertical
R6, R9: 1K; R_Axial_DIN0309_L9.0mm_D3.2mm_P2.54mm_Vertical
U1: 74HC00
U2, U4: SN74AVC8T245PW; SOP-24_7.5x15.4mm_P1.27mm
U3: Pico; RPi_Pico_SMD_TH

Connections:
+3.3V: C5.1, C6.1, C7.1, U2.23 (VCCB), U2.24 (VCCB), U3.40 (VBUS), U4.23 (VCCB), U4.24 (VCCB)
+5V: C1.1, C2.1, C3.1, C4.1, J1.24, J1.25, R1.1, U1.14 (VCC), U2.1 (VCCA), U3.39 (VSYS), U4.1 (VCCA)
/B: J2.3, R4.2, R5.2
/B0: R4.1, U3.19 (GPIO14)
/B1: R5.1, U3.20 (GPIO15)
/G: J2.2, R6.2, R7.2, R8.2
/G0: R8.1, U3.21 (GPIO16)
/G1: R7.1, U3.22 (GPIO17)
/G2: R6.1, U3.24 (GPIO18)
/HSYNC: R3.1, U3.31 (GPIO26_ADC0)
/R: J2.1, R9.2, R10.2, R11.2
/R0: R9.1, U3.25 (GPIO19)
/R1: R10.1, U3.26 (GPIO20)
/R2: R11.1, U3.27 (GPIO21)
/RUN: U2.14 (B8), U3.30 (RUN)
/RW: U2.15 (B7), U3.29 (GPIO22)
/VSYNC: R2.1, U3.32 (GPIO27_ADC1)
A0: J1.1, U2.3 (A1)
A1: J1.3, U2.4 (A2)
A2: J1.5, U2.5 (A3)
A3: J1.7, U2.6 (A4)
A4: J1.9
A5: J1.11
A6: J1.13
A7: J1.15
A8: J1.17
A9: J1.19
A10: J1.21
A11: J1.27
A12: J1.29
A13: J1.31
A14: J1.33
A15: J1.35
BE: J1.39
CLK: J1.41, U2.8 (A6)
CLK_12M: J1.42
D0: J1.2, U4.3 (A1)
D1: J1.4, U4.4 (A2)
D2: J1.6, U4.5 (A3)
D3: J1.8, U4.6 (A4)
D4: J1.10, U4.7 (A5)
D5: J1.12, U4.8 (A6)
D6: J1.14, U4.9 (A7)
D7: J1.16, U4.10 (A8)
EX0: J1.18
EX1: J1.20
EX2: J1.44
EX3: J1.46
GND: C1.2, C2.2, C3.2, C4.2, C5.2, C6.2, C7.2, J1.23, J1.26, J2.0, J2.5, J2.6, J2.7, J2.8, U1.4, U1.5, U1.7 (GND), U1.9, U1.10, U1.12, U1.13, U2.11 (GND), U2.12 (GND), U2.13 (GND), U3.3 (GND), U3.8 (GND), U3.13 (GND), U3.18 (GND), U3.23 (GND), U3.28 (GND), U3.38 (GND), U3.42 (GND), U4.11 (GND), U4.12 (GND), U4.13 (GND)
LED1: J1.34
LED2: J1.36
LED3: J1.38
LED4: J1.40
unnamed: J2.13, R3.2
unnamed: J2.14, R2.2
unnamed: U2.21 (B1), U3.1 (GPIO0)
unnamed: U2.20 (B2), U3.2 (GPIO1)
unnamed: U2.19 (B3), U3.4 (GPIO2)
unnamed: U2.18 (B4), U3.5 (GPIO3)
unnamed: U2.17 (B5), U3.16 (GPIO12)
unnamed: U2.16 (B6), U3.17 (GPIO13)
unnamed: R1.2, U2.2 (DIR)
unnamed: U3.6 (GPIO4), U4.21 (B1)
unnamed: U3.7 (GPIO5), U4.20 (B2)
unnamed: U3.9 (GPIO6), U4.19 (B3)
unnamed: U3.10 (GPIO7), U4.18 (B4)
unnamed: U3.11 (GPIO8), U4.17 (B5)
unnamed: U3.12 (GPIO9), U4.16 (B6)
unnamed: U3.14 (GPIO10), U4.15 (B7)
unnamed: U3.15 (GPIO11), U4.14 (B8)
unnamed: U1.3, U4.2 (DIR)
RDY: J1.37
R~W: J1.43, U1.1, U1.2, U2.9 (A7)
SYNC: J1.47
~INH: J1.30
~IRQ: J1.45
~NMI: J1.50
~RESET: J1.49, U2.10 (A8)
~SLOT_IRQ: J1.48, U3.34 (GPIO28_ADC2)
~SLOT_SEL: J1.32, U2.7 (A5), U2.22 (~OE), U4.22 (~OE)
~SLOW: J1.22
~SSEL: J1.28

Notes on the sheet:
DIR high : A -> B DIR low : B -> A

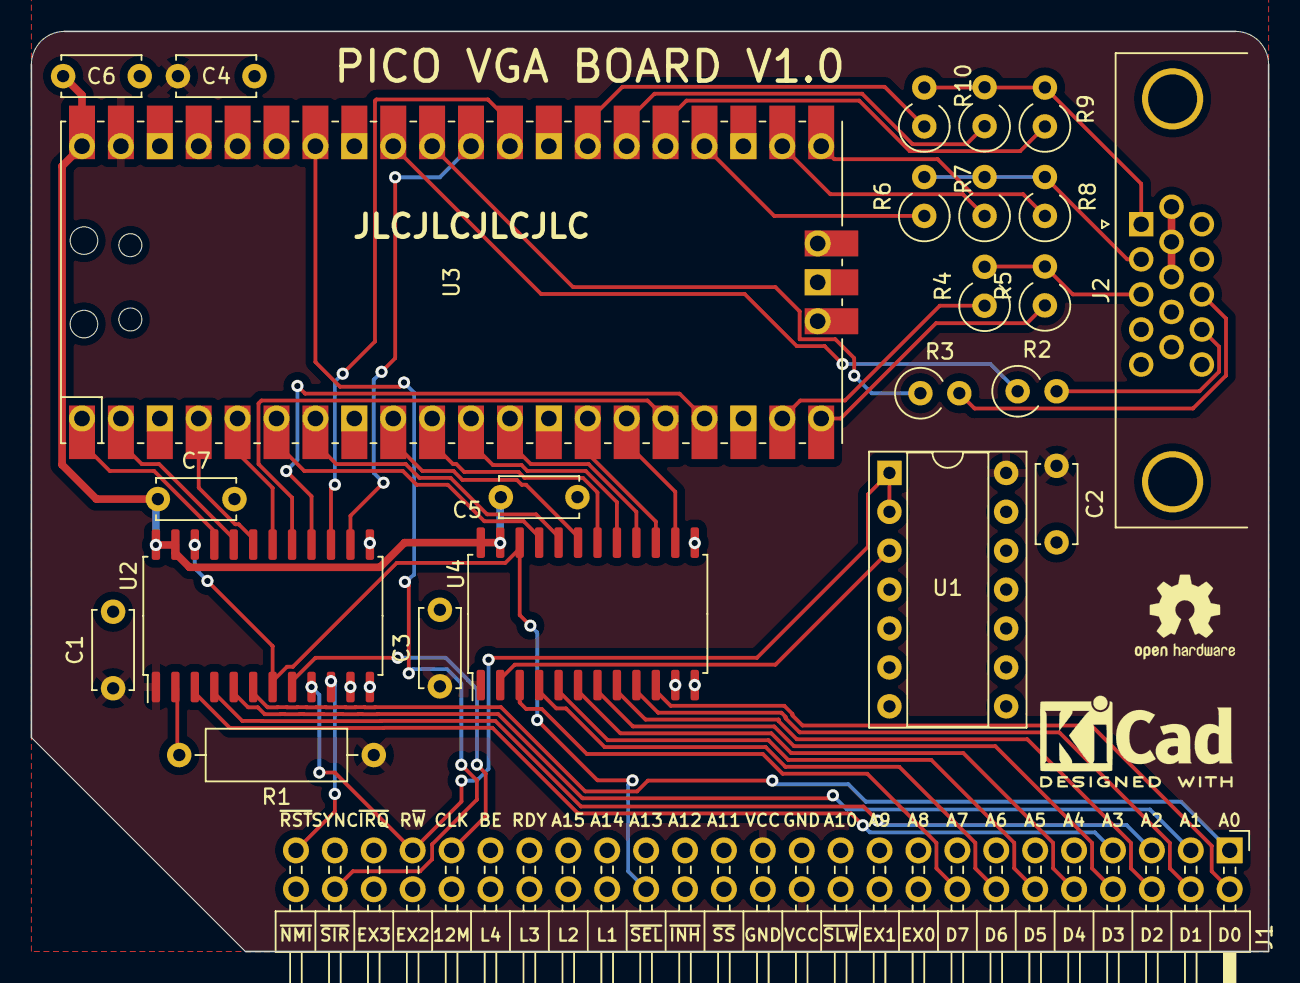
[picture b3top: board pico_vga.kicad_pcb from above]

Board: 2 copper layers, 80.8 x 60.1 mm, 24 parts (0 on the bottom side), 53 nets.

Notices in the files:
Hardware/mainboard/mainboard.kicad_pcb:
©Jonathan Foucher 2021
README.md:
CERN-OHL-1.2 GPL-3.0-or-later CC-BY-SA-4.0
